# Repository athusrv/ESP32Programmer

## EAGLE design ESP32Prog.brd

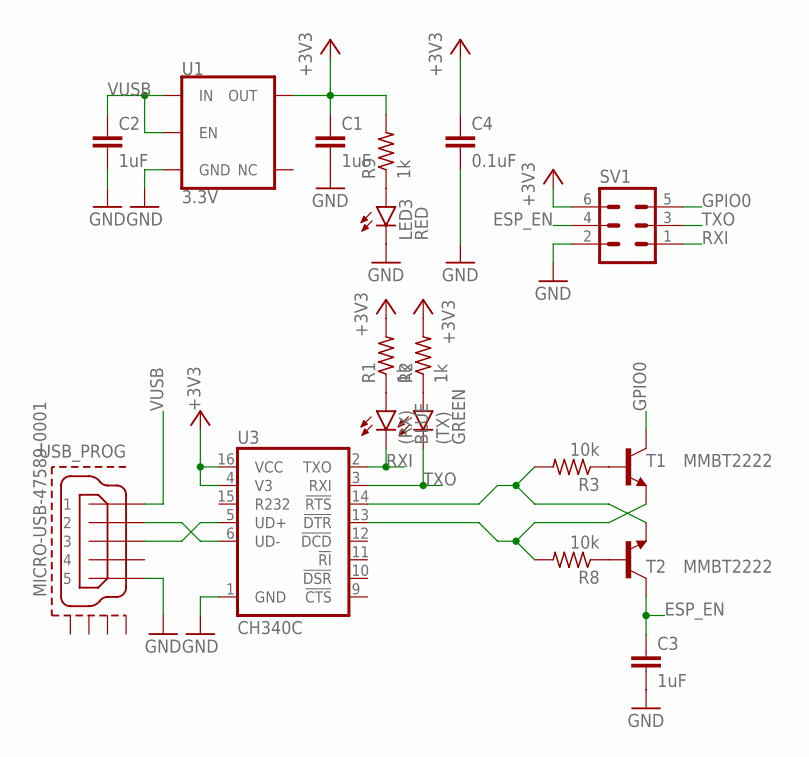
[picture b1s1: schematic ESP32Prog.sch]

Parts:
(RX): BLUE; CHIP-LED0603
(TX): GREEN; CHIP-LED0603
C1, C2, C3: 1uF; C0603K
C4: 0.1uF; C0603K
LED3: RED; CHIP-LED0603
R1, R2, R9: 1k; R0402
R3, R8: 10k; R0402
SV1: MA03-2
T1, T2: MMBT2222; SOT23-BEC
U1: 3.3V; SOT23-5
U3: CH340C; SO016
USB_PROG: MICRO-USB-47589-0001; 47589-0001

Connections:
+3V3: C1.1, C4.1, R1.2, R2.2, R9.2, SV1.6, U1.5 (OUT), U3.4 (V3), U3.16 (VCC)
DTR: R8.2, T1.E, U3.13 (!DTR)
ESP_EN: C3.1, SV1.4, T2.C
GND: C1.2, C2.2, C3.2, C4.2, LED3.C, SV1.2, U1.2 (GND), U3.1 (GND), USB_PROG.5
GPIO0: SV1.5, T1.C
unnamed: (RX).A, R1.1
unnamed: U3.6 (UD-), USB_PROG.2
unnamed: U3.5 (UD+), USB_PROG.3
unnamed: (TX).A, R2.1
unnamed: R3.1, T1.B
unnamed: R8.1, T2.B
unnamed: LED3.A, R9.1
RTS: R3.2, T2.E, U3.14 (!RTS)
RXI: (RX).C, SV1.1, U3.2 (TXO)
TXO: (TX).C, SV1.3, U3.3 (RXI)
VUSB: C2.1, U1.1 (IN), U1.3 (EN), USB_PROG.1

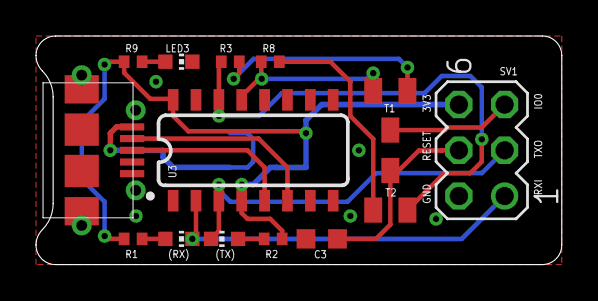
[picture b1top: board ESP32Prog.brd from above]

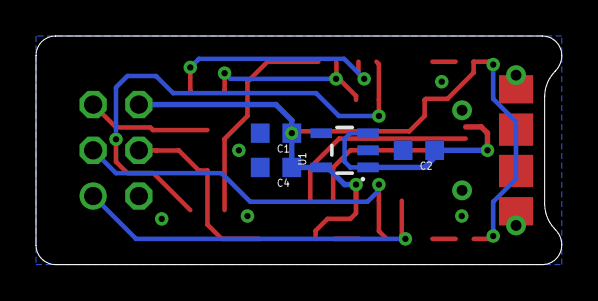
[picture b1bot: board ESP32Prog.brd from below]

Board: 2 copper layers, 29.2 x 12.7 mm, 18 parts (4 on the bottom side), 16 nets.

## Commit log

2020-07-17 fixed gnd pin

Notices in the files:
parts and their libraries:
con-molex-usb: (C) 2014 Tomasz Boleslaw CEDRO, cederom@tlen.pl, http://www.tomek.cedro.info.
SparkFun-IC-Power: Licensing: Creative Commons ShareAlike 4.0 International - https://creativecommons.org/licenses/by-sa/4.0
